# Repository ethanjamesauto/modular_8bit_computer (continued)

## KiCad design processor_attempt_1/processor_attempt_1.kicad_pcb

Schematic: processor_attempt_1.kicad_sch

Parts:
5V_rsns1: 1; R_1206_3216Metric
C1, C2: C; C_1206_3216Metric
C3, C4, C5, C6, C7, C9, C10, C11, C15, C16, C17, C18: 100nF; C_Disc_D3.0mm_W1.6mm_P2.50mm
D1, D17, D25, D33, D41, D49, D50, D51, D52, D53, D54, D55, D56, D57, D58, D59, D60, D61, D62, D63, D64, D65, D66, D67, D68, D69, D70, D71, D72, D73, D74, D75, D76, D77, D78, D79, D80: A0; LED_0603_1608Metric_Pad1.05x0.95mm_HandSolder
D2, D18, D26, D34, D42: A1; LED_0603_1608Metric_Pad1.05x0.95mm_HandSolder
D3, D19, D27, D35, D43: A2; LED_0603_1608Metric_Pad1.05x0.95mm_HandSolder
D4, D20, D28, D36, D44: A3; LED_0603_1608Metric_Pad1.05x0.95mm_HandSolder
D5, D21, D29, D37, D45: A4; LED_0603_1608Metric_Pad1.05x0.95mm_HandSolder
D6, D22, D30, D38, D46: A5; LED_0603_1608Metric_Pad1.05x0.95mm_HandSolder
D7, D23, D31, D39, D47: A6; LED_0603_1608Metric_Pad1.05x0.95mm_HandSolder
D8, D24, D32, D40, D48: A7; LED_0603_1608Metric_Pad1.05x0.95mm_HandSolder
D9: A8; LED_0603_1608Metric_Pad1.05x0.95mm_HandSolder
D10: A9; LED_0603_1608Metric_Pad1.05x0.95mm_HandSolder
D11: A10; LED_0603_1608Metric_Pad1.05x0.95mm_HandSolder
D12: A11; LED_0603_1608Metric_Pad1.05x0.95mm_HandSolder
D13: A12; LED_0603_1608Metric_Pad1.05x0.95mm_HandSolder
D14: A13; LED_0603_1608Metric_Pad1.05x0.95mm_HandSolder
D15: A14; LED_0603_1608Metric_Pad1.05x0.95mm_HandSolder
D16: A15; LED_0603_1608Metric_Pad1.05x0.95mm_HandSolder
D81: 5V_RAW; LED_0603_1608Metric_Pad1.05x0.95mm_HandSolder
J1: Conn_01x03_Pin; PinHeader_1x03_P2.54mm_Vertical
J2: Conn_Coaxial; BNC_TEConnectivity_1478204_Vertical; not fitted
J3: Conn_01x40_Pin; PinHeader_1x40_P2.54mm_Horizontal
J4, J20, J22, J23, J24, J25, J26, J27, J28, J29: Conn_01x08_Pin; PinHeader_1x08_P2.54mm_Vertical
J5, J6: Conn_01x08_Pin; PinHeader_1x08_P2.54mm_Vertical; not fitted
J7, J8, J9, J10, J11, J12, J13, J18, J19: Conn_01x10_Pin; PinHeader_1x10_P2.54mm_Vertical
J14, J15, J16, J17: Conn_01x06_Pin; PinHeader_1x06_P2.54mm_Vertical
J21: DB9_Female_MountingHoles; DSUB-9_Female_Horizontal_P2.77x2.84mm_EdgePinOffset4.94mm_H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
Q1, Q2, Q3, Q4, Q5, Q6, Q7, Q8, Q9, Q10, Q11, Q12: FDG1024NZ; SOT-23-6_Handsoldering
R1, R2: R; R_0603_1608Metric_Pad0.98x0.95mm_HandSolder
R3, R4, R6, R7, R11, R12, R13, R14, R19, R20, R21, R22, R27, R28, R29, R30, R35, R36, R37, R38, R39, R40, R41, R42, R99, R100, R101, R102: 10k; R_0603_1608Metric_Pad0.98x0.95mm_HandSolder
R5, R8, R9, R10, R15, R16, R17, R18, R23, R24, R25, R26, R31, R32, R33, R34, R43, R44, R45, R46, R47, R48, R49, R50: 1k; R_0603_1608Metric_Pad0.98x0.95mm_HandSolder
R103, R104, R105, R106: 0; R_0603_1608Metric_Pad0.98x0.95mm_HandSolder
U1: NE555D; DIP-8_W7.62mm_Socket
U2, U3, U4, U5: 74LS161; DIP-16_W7.62mm_Socket
U6, U7, U25, U26, U27, U44, U45, U47, U54: 74LS574; DIP-20_W7.62mm_Socket
U8, U9, U10, U11: 74LS161; DIP-16_W7.62mm_Socket; not fitted
U12, U13, U14, U15: 74LS257; DIP-16_W7.62mm_Socket; not fitted
U16, U17, U22: 74LS245; DIP-20_W7.62mm_Socket; not fitted
U18, U19: 28C256; DIP-28_W15.24mm_Socket
U20: 74LS574; DIP-20_W7.62mm_Socket; not fitted
U21, U23, U29, U30, U31, U48, U49, U50: 74LS245; DIP-20_W7.62mm_Socket
U24, U40, U41: 74LS273; DIP-20_W7.62mm_Socket
U28: HM62256BLP; DIP-28_W15.24mm
U32, U39: 74LS283; DIP-16_W7.62mm_Socket
U33, U34, U35, U36, U37, U38: DIP-16_W7.62mm_Socket
U42, U56: 74LS04; DIP-14_W7.62mm_Socket
U43: 74HC688; DIP-20_W7.62mm_Socket
U46: HM62256BLP; SOIC-28W_7.5x18.7mm_P1.27mm
U51: 74LS161; SOIC-16_3.9x9.9mm_P1.27mm
U52, U53: 74LS00; DIP-14_W7.62mm_Socket
U55: 74LS30; DIP-14_W7.62mm_Socket
U57, U58, U59, U60: 74LS138; DIP-16_W7.62mm_Socket
U61: 74LVC1G08; SOT-23-6_Handsoldering
r51, r52, r53, r54, r55, r56, r57, r58, r59, r60, r61, r62, r63, r64, r65, r66, r67, r68, r69, r70, r71, r72, r73, r74, r75, r76, r77, r78, r79, r80, r81, r82, r83, r84, r85, r86, r87, r88, r89, r90, r91, r92, r93, r94, r95, r96, r97, r98, r107, r108, r109, r110, r111, r112, r113, r114, r115, r116, r117, r118, r119, r120, r121, r122, r123, r124, r125, r126, r127, r128, r129, r130, r131, r132, r133, r134, r135, r136, r137, r138, r139: 470; R_0603_1608Metric_Pad0.98x0.95mm_HandSolder

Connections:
+3V3: J3.5
+5V: 5V_rsns1.2, C3.1, C4.1, C5.1, C6.1, C7.1, C9.1, C10.1, C11.1, C15.1, C16.1, C17.1, C18.1, R1.1, R5.2, R8.2, R9.2, R10.2, R15.2, R16.2, R17.2, R18.2, R23.2, R24.2, R25.2, R26.2, R31.2, R32.2, R33.2, R34.2, R43.2, R44.2, R45.2, R46.2, R47.2, R48.2, R49.2, R50.2, U1.4 (R), U1.8 (VCC), U2.7 (CEP), U2.16 (VCC), U3.7 (CEP), U3.16 (VCC), U4.7 (CEP), U4.16 (VCC), U5.7 (CEP), U5.16 (VCC), U6.20 (VCC), U7.20 (VCC), U18.28 (VCC), U19.28 (VCC), U21.20 (VCC), U23.20 (VCC), U24.20 (VCC), U25.20 (VCC), U26.20 (VCC), U27.20 (VCC), U28.28 (VCC), U29.20 (VCC), U30.20 (VCC), U31.20 (VCC), U32.16 (VCC), U33.16 (VCC), U34.16 (VCC), U35.16 (VCC), U36.16 (VCC), U37.16 (VCC), U38.16 (VCC), U39.16 (VCC), U40.20 (VCC), U41.20 (VCC), U42.14 (VCC), U43.20 (VCC), U44.20 (VCC), U45.20 (VCC), U46.28 (VCC), U47.20 (VCC), U48.20 (VCC), U49.20 (VCC), U50.20 (VCC), U51.16 (VCC), U52.14 (VCC), U53.14 (VCC), U54.20 (VCC), U55.14 (VCC), U56.14 (VCC), U57.6 (E3), U57.16 (VCC), U58.16 (VCC), U59.16 (VCC), U60.16 (VCC), U61.5 (VCC)
/5V_raw: 5V_rsns1.1, J3.1, U61.4, r139.2
/APB_0: J20.8, U32.4 (S1), U49.18 (B0)
/APB_1: J20.7, U32.1 (S2), U49.17 (B1)
/APB_2: J20.6, U32.13 (S3), U49.16 (B2)
/APB_3: J20.5, U32.10 (S4), U49.15 (B3)
/APB_4: J20.4, U39.4 (S1), U49.14 (B4)
/APB_5: J20.3, U39.1 (S2), U49.13 (B5)
/APB_6: J20.2, U39.13 (S3), U49.12 (B6)
/APB_7: J20.1, U39.10 (S4), U49.11 (B7)
/A_nand_B_0: U50.18 (B0), U52.3
/A_nand_B_1: U50.17 (B1), U52.6
/A_nand_B_2: U50.16 (B2), U52.8
/A_nand_B_3: U50.15 (B3), U52.11
/A_nand_B_4: U50.14 (B4), U53.3
/A_nand_B_5: U50.13 (B5), U53.6
/A_nand_B_6: U50.12 (B6), U53.8
/A_nand_B_7: U50.11 (B7), U53.11
/Aux_Bus_0_LSB: J3.33, J4.1, U21.2 (A0), U25.9 (D7), U26.9 (D7)
/Aux_Bus_1: J3.34, J4.2, U21.3 (A1), U25.8 (D6), U26.8 (D6)
/Aux_Bus_2: J3.35, J4.3, U21.4 (A2), U25.7 (D5), U26.7 (D5)
/Aux_Bus_3: J3.36, J4.4, U21.5 (A3), U25.6 (D4), U26.6 (D4)
/Aux_Bus_4: J3.37, J4.5, U21.6 (A4), U25.5 (D3), U26.5 (D3)
/Aux_Bus_5: J3.38, J4.6, U21.7 (A5), U25.4 (D2), U26.4 (D2)
/Aux_Bus_6: J3.39, J4.7, U21.8 (A6), U25.3 (D1), U26.3 (D1)
/Aux_Bus_7_MSB: J3.40, J4.8, U21.9 (A7), U25.2 (D0), U26.2 (D0)
/CLOCK_to_pc: J1.2, U2.2 (CP), U3.2 (CP), U4.2 (CP), U5.2 (CP), U8.2 (CP), U9.2 (CP), U10.2 (CP), U11.2 (CP)
/Data_Bus_0_LSB: J3.9, J11.2, Q9.3 (D), R43.1, U27.9 (D7)
/Data_Bus_1: J3.10, J11.3, Q9.6 (D), R44.1, U27.8 (D6)
/Data_Bus_2: J3.11, J11.4, Q10.3 (D), R45.1, U27.7 (D5)
/Data_Bus_3: J3.12, J11.5, Q10.6 (D), R46.1, U27.6 (D4)
/Data_Bus_4: J3.13, J11.6, Q11.3 (D), R47.1, U27.5 (D3)
/Data_Bus_5: J3.14, J11.7, Q11.6 (D), R48.1, U27.4 (D2)
/Data_Bus_6: J3.15, J11.8, Q12.3 (D), R49.1, U27.3 (D1)
/Data_Bus_7_MSB: J3.16, J11.9, Q12.6 (D), R50.1, U27.2 (D0)
/INTERNAL_BUS_0: J7.2, J8.2, J12.2, J13.2, J19.8, J21.6, U6.2 (D0), U7.2 (D0), U25.12 (Q7), U26.12 (Q7), U27.12 (Q7), U28.11 (Q0), U29.11 (B7), U30.11 (B7), U31.18 (B0), U38.12 (D3), U40.3 (D0), U41.3 (D0), U44.19 (Q0), U45.19 (Q0), U46.11 (Q0), U47.19 (Q0), U48.18 (B0), U49.2 (A0), U50.2 (A0), U51.3 (D0), U54.19 (Q0), r67.2
/INTERNAL_BUS_1: J7.3, J8.3, J12.3, J13.3, J19.7, J21.7, U6.3 (D1), U7.3 (D1), U25.13 (Q6), U26.13 (Q6), U27.13 (Q6), U28.12 (Q1), U29.12 (B6), U30.12 (B6), U31.17 (B1), U38.10 (D2), U40.4 (D1), U41.4 (D1), U44.18 (Q1), U45.18 (Q1), U46.12 (Q1), U47.18 (Q1), U48.17 (B1), U49.3 (A1), U50.3 (A1), U51.4 (D1), U54.18 (Q1), r68.2
/INTERNAL_BUS_2: J7.4, J8.4, J12.4, J13.4, J19.6, J21.8, U6.4 (D2), U7.4 (D2), U25.14 (Q5), U26.14 (Q5), U27.14 (Q5), U28.13 (Q2), U29.13 (B5), U30.13 (B5), U31.16 (B2), U38.6 (D1), U40.7 (D2), U41.7 (D2), U44.17 (Q2), U45.17 (Q2), U46.13 (Q2), U47.17 (Q2), U48.16 (B2), U49.4 (A2), U50.4 (A2), U51.5 (D2), U54.17 (Q2), r69.2
/INTERNAL_BUS_3: J7.5, J8.5, J12.5, J13.5, J19.5, J21.9, U6.5 (D3), U7.5 (D3), U25.15 (Q4), U26.15 (Q4), U27.15 (Q4), U28.15 (Q3), U29.14 (B4), U30.14 (B4), U31.15 (B3), U38.4 (D0), U40.8 (D3), U41.8 (D3), U44.16 (Q3), U45.16 (Q3), U46.15 (Q3), U47.16 (Q3), U48.15 (B3), U49.5 (A3), U50.5 (A3), U51.6 (D3), U54.16 (Q3), r70.2
/INTERNAL_BUS_4: J7.6, J8.6, J12.6, J13.6, J19.4, J21.5, U6.6 (D4), U7.6 (D4), U25.16 (Q3), U26.16 (Q3), U27.16 (Q3), U28.16 (Q4), U29.15 (B3), U30.15 (B3), U31.14 (B4), U37.12 (D3), U40.13 (D4), U41.13 (D4), U44.15 (Q4), U45.15 (Q4), U46.16 (Q4), U47.15 (Q4), U48.14 (B4), U49.6 (A4), U50.6 (A4), U54.15 (Q4), r71.2
/INTERNAL_BUS_5: J7.7, J8.7, J12.7, J13.7, J19.3, J21.4, U6.7 (D5), U7.7 (D5), U25.17 (Q2), U26.17 (Q2), U27.17 (Q2), U28.17 (Q5), U29.16 (B2), U30.16 (B2), U31.13 (B5), U37.10 (D2), U40.14 (D5), U41.14 (D5), U44.14 (Q5), U45.14 (Q5), U46.17 (Q5), U47.14 (Q5), U48.13 (B5), U49.7 (A5), U50.7 (A5), U54.14 (Q5), r72.2
/INTERNAL_BUS_6: J7.8, J8.8, J12.8, J13.8, J19.2, J21.3, U6.8 (D6), U7.8 (D6), U25.18 (Q1), U26.18 (Q1), U27.18 (Q1), U28.18 (Q6), U29.17 (B1), U30.17 (B1), U31.12 (B6), U37.6 (D1), U40.17 (D6), U41.17 (D6), U44.13 (Q6), U45.13 (Q6), U46.18 (Q6), U47.13 (Q6), U48.12 (B6), U49.8 (A6), U50.8 (A6), U54.13 (Q6), r73.2
/INTERNAL_BUS_7: J7.9, J8.9, J12.9, J13.9, J19.1, J21.2, U6.9 (D7), U7.9 (D7), U25.19 (Q0), U26.19 (Q0), U27.19 (Q0), U28.19 (Q7), U29.18 (B0), U30.18 (B0), U31.11 (B7), U37.4 (D0), U40.18 (D7), U41.18 (D7), U44.12 (Q7), U45.12 (Q7), U46.19 (Q7), U47.12 (Q7), U48.11 (B7), U49.9 (A7), U50.9 (A7), U54.12 (Q7), r74.2
/PC_0: U2.14 (Q0), U16.2 (A0), U30.9 (A7), r51.2
/PC_1: U2.13 (Q1), U16.3 (A1), U18.10 (A0), U19.10 (A0), U30.8 (A6), r52.2
/PC_2: U2.12 (Q2), U16.4 (A2), U18.9 (A1), U19.9 (A1), U30.7 (A5), r53.2
/PC_3: U2.11 (Q3), U16.5 (A3), U18.8 (A2), U19.8 (A2), U30.6 (A4), r54.2
/PC_4: U3.14 (Q0), U16.6 (A4), U18.7 (A3), U19.7 (A3), U30.5 (A3), r55.2
/PC_5: U3.13 (Q1), U16.7 (A5), U18.6 (A4), U19.6 (A4), U30.4 (A2), r56.2
/PC_6: U3.12 (Q2), U16.8 (A6), U18.5 (A5), U19.5 (A5), U30.3 (A1), r57.2
/PC_7: U3.11 (Q3), U16.9 (A7), U18.4 (A6), U19.4 (A6), U30.2 (A0), r58.2
/PC_8: U4.14 (Q0), U18.3 (A7), U19.3 (A7), U29.9 (A7), r59.2
/PC_9: U4.13 (Q1), U18.25 (A8), U19.25 (A8), U29.8 (A6), r60.2
/PC_10: U4.12 (Q2), U18.24 (A9), U19.24 (A9), U29.7 (A5), r61.2
/PC_11: U4.11 (Q3), U18.21 (A10), U19.21 (A10), U29.6 (A4), r62.2
/PC_12: U5.14 (Q0), U18.23 (A11), U19.23 (A11), U29.5 (A3), r63.2
/PC_13: U5.13 (Q1), U18.2 (A12), U19.2 (A12), U29.4 (A2), r64.2
/PC_14: U5.12 (Q2), U18.26 (A13), U19.26 (A13), U29.3 (A1), r65.2
/PC_15: U5.11 (Q3), U18.1 (A14), U19.1 (A14), U29.2 (A0), r66.2
/PC_load_n: U2.9 (~PE), U3.9 (~PE), U4.9 (~PE), U5.9 (~PE)
/RA_0: U32.5 (A1), U40.2 (Q0), U52.2, r83.2
/RA_1: U32.3 (A2), U40.5 (Q1), U52.4, r84.2
/RA_2: U32.14 (A3), U40.6 (Q2), U52.10, r85.2
/RA_3: U32.12 (A4), U40.9 (Q3), U52.12, r86.2
/RA_4: U39.5 (A1), U40.12 (Q4), U53.2, r87.2
/RA_5: U39.3 (A2), U40.15 (Q5), U53.4, r88.2
/RA_6: U39.14 (A3), U40.16 (Q6), U53.10, r89.2
/RA_7: U39.12 (A4), U40.19 (Q7), U53.12, r90.2
/RB_0: U32.6 (B1), U41.2 (Q0), U52.1, r91.2
/RB_1: U32.2 (B2), U41.5 (Q1), U52.5, r92.2
/RB_2: U32.15 (B3), U41.6 (Q2), U52.9, r93.2
/RB_3: U32.11 (B4), U41.9 (Q3), U52.13, r94.2
/RB_4: U39.6 (B1), U41.12 (Q4), U53.1, r95.2
/RB_5: U39.2 (B2), U41.15 (Q5), U53.5, r96.2
/RB_6: U39.15 (B3), U41.16 (Q6), U53.9, r97.2
/RB_7: U39.11 (B4), U41.19 (Q7), U53.13, r98.2
/RC_0: U43.12 (R4), U48.8 (A6), U54.2 (D0), U55.2
/RC_1: U43.14 (R5), U48.6 (A4), U54.3 (D1), U55.1
/RC_2: U43.16 (R6), U48.4 (A2), U54.4 (D2), U55.12
/RC_3: U43.18 (R7), U48.2 (A0), U54.5 (D3), U55.11
/RC_4: U43.3 (R0), U54.6 (D4), U55.6
/RC_5: U43.5 (R1), U54.7 (D5), U55.5
/RC_6: U43.7 (R2), U54.8 (D6), U55.4
/RC_7: U43.9 (R3), U54.9 (D7), U55.3
/RD_0: U43.11 (P4), U47.2 (D0), U48.9 (A7)
/RD_1: U43.13 (P5), U47.3 (D1), U48.7 (A5)
/RD_2: U43.15 (P6), U47.4 (D2), U48.5 (A3)
/RD_3: U43.17 (P7), U47.5 (D3), U48.3 (A1)
/RD_4: U43.2 (P0), U47.6 (D4)
/RD_5: U43.4 (P1), U47.7 (D5)
/RD_6: U43.6 (P2), U47.8 (D6)
/RD_7: U43.8 (P3), U47.9 (D7)
/SMALL_CS2: U46.26 (A13)
/addr_bus_0: J3.17, Q1.3 (D), R5.1
/addr_bus_1: J3.18, Q1.6 (D), R8.1
/addr_bus_2: J3.19, Q2.3 (D), R9.1
/addr_bus_3: J3.20, Q2.6 (D), R10.1
/addr_bus_4: J3.21, Q3.3 (D), R15.1
/addr_bus_5: J3.22, Q3.6 (D), R16.1
/addr_bus_6: J3.23, Q4.3 (D), R17.1
/addr_bus_7: J3.24, Q4.6 (D), R18.1
/addr_bus_8: J3.25, Q5.3 (D), R23.1
/addr_bus_9: J3.26, Q5.6 (D), R24.1
/addr_bus_10: J3.27, Q6.3 (D), R25.1
/addr_bus_11: J3.28, Q6.6 (D), R26.1
/addr_bus_12: J3.29, Q7.3 (D), R31.1
/addr_bus_13: J3.30, Q7.6 (D), R32.1
/addr_bus_14: J3.31, Q8.3 (D), R33.1
/addr_bus_15: J3.32, Q8.6 (D), R34.1
/addr_bus_select_0: R99.2, R103.2, U33.1 (A0), U34.1 (A0), U35.1 (A0), U36.1 (A0), U37.1 (A0), U38.1 (A0)
/addr_bus_select_1: R100.2, R104.2, U33.15 (A1), U34.15 (A1), U35.15 (A1), U36.15 (A1), U37.15 (A1), U38.15 (A1)
/addr_bus_select_2: R101.2, R105.2, U33.14 (A2), U34.14 (A2), U35.14 (A2), U36.14 (A2), U37.14 (A2), U38.14 (A2)
/addr_bus_select_3: R102.2, R106.2, U33.13 (A3), U34.13 (A3), U35.13 (A3), U36.13 (A3), U37.13 (A3), U38.13 (A3)
/addr_oe_n: U33.2 (~CS), U34.2 (~CS), U35.2 (~CS), U36.2 (~CS), U37.2 (~CS), U38.2 (~CS)
/addr_to_driver_0: Q1.5 (G), R4.2, U33.11 (S3_n)
/addr_to_driver_1: Q1.2 (G), R7.2, U33.9 (S2_n)
/addr_to_driver_2: Q2.5 (G), R3.2, U33.7 (S1_n)
/addr_to_driver_3: Q2.2 (G), R6.2, U33.5 (S0_n)
/addr_to_driver_4: Q3.5 (G), R11.2, U35.11 (S3_n)
/addr_to_driver_5: Q3.2 (G), R12.2, U35.9 (S2_n)
/addr_to_driver_6: Q4.5 (G), R13.2, U35.7 (S1_n)
/addr_to_driver_7: Q4.2 (G), R14.2, U35.5 (S0_n)
/addr_to_driver_8: Q5.5 (G), R19.2, U34.11 (S3_n)
/addr_to_driver_9: Q5.2 (G), R20.2, U34.9 (S2_n)
/addr_to_driver_10: Q6.5 (G), R21.2, U34.7 (S1_n)
/addr_to_driver_11: Q6.2 (G), R22.2, U34.5 (S0_n)
/addr_to_driver_12: Q7.5 (G), R27.2, U36.11 (S3_n)
/addr_to_driver_13: Q7.2 (G), R28.2, U36.9 (S2_n)
/addr_to_driver_14: Q8.5 (G), R29.2, U36.7 (S1_n)
/addr_to_driver_15: Q8.2 (G), R30.2, U36.5 (S0_n)
/addr_we_n: U33.3 (~WE), U34.3 (~WE), U35.3 (~WE), U36.3 (~WE)
/clk: J3.3
/ctrl_0: J23.8, J27.8, U57.15 (O0), r138.2
/ctrl_1: J23.7, J27.7, U57.14 (O1), r137.2
/ctrl_2: J23.6, J27.6, U57.13 (O2), r136.2
/ctrl_3: J23.5, J27.5, U57.12 (O3), r135.2
/ctrl_4: J23.4, J27.4, U57.11 (O4), r134.2
/ctrl_5: J23.3, J27.3, U57.10 (O5), r133.2
/ctrl_6: J23.2, J27.2, U57.9 (O6), r132.2
/ctrl_7: J23.1, J27.1, U57.7 (O7), r131.2
/ctrl_8: J22.8, J24.8, U58.15 (O0), r130.2
/ctrl_9: J22.7, J24.7, U58.14 (O1), r129.2
/ctrl_10: J22.6, J24.6, U58.13 (O2), r128.2
/ctrl_11: J22.5, J24.5, U58.12 (O3), r127.2
/ctrl_12: J22.4, J24.4, U58.11 (O4), r126.2
/ctrl_13: J22.3, J24.3, U58.10 (O5), r125.2
/ctrl_14: J22.2, J24.2, U58.9 (O6), r124.2
/ctrl_15: J22.1, J24.1, U58.7 (O7), r123.2
/ctrl_16: J26.8, J28.8, U59.15 (O0), r107.2
/ctrl_17: J26.7, J28.7, U59.14 (O1), r108.2
/ctrl_18: J26.6, J28.6, U59.13 (O2), r109.2
/ctrl_19: J26.5, J28.5, U59.12 (O3), r110.2
/ctrl_20: J26.4, J28.4, U59.11 (O4), r111.2
/ctrl_21: J26.3, J28.3, U59.10 (O5), r112.2
/ctrl_22: J26.2, J28.2, U59.9 (O6), r113.2
/ctrl_23: J26.1, J28.1, U59.7 (O7), r114.2
/ctrl_24: J25.8, J29.8, U60.15 (O0), r115.2
/ctrl_25: J25.7, J29.7, U60.14 (O1), r116.2
/ctrl_26: J25.6, J29.6, U60.13 (O2), r117.2
/ctrl_27: J25.5, J29.5, U60.12 (O3), r118.2
/ctrl_28: J25.4, J29.4, U60.11 (O4), r119.2
/ctrl_29: J25.3, J29.3, U60.10 (O5), r120.2
/ctrl_30: J25.2, J29.2, U60.9 (O6), r121.2
/ctrl_31: J25.1, J29.1, U60.7 (O7), r122.2
/current_sense_output: U61.1
/data_to_driver_0: Q9.5 (G), R35.2, U38.11 (S3_n)
/data_to_driver_1: Q9.2 (G), R36.2, U38.9 (S2_n)
/data_to_driver_2: Q10.5 (G), R37.2, U38.7 (S1_n)
/data_to_driver_3: Q10.2 (G), R38.2, U38.5 (S0_n)
/data_to_driver_4: Q11.5 (G), R39.2, U37.11 (S3_n)
/data_to_driver_5: Q11.2 (G), R40.2, U37.9 (S2_n)
/data_to_driver_6: Q12.5 (G), R41.2, U37.7 (S1_n)
/data_to_driver_7: Q12.2 (G), R42.2, U37.5 (S0_n)
/data_we_n: U37.3 (~WE), U38.3 (~WE)
/decoder_neg_clock: U60.5 (E2)
/decoder_pos_clock: U59.6 (E3)
/instruction_0: J18.2, U18.11 (D0), U19.11 (D0), U20.19 (Q0), U21.18 (B0), U22.18 (B0), U23.2 (A0), U24.3 (D0), U31.2 (A0), r75.2
/instruction_1: J18.3, U18.12 (D1), U19.12 (D1), U20.18 (Q1), U21.17 (B1), U22.17 (B1), U23.3 (A1), U24.4 (D1), U31.3 (A1), r76.2
/instruction_2: J18.4, U18.13 (D2), U19.13 (D2), U20.17 (Q2), U21.16 (B2), U22.16 (B2), U23.4 (A2), U24.7 (D2), U31.4 (A2), r77.2
/instruction_3: J18.5, U18.15 (D3), U19.15 (D3), U20.16 (Q3), U21.15 (B3), U22.15 (B3), U23.5 (A3), U24.8 (D3), U31.5 (A3), r78.2
/instruction_4: J18.6, U18.16 (D4), U19.16 (D4), U20.15 (Q4), U21.14 (B4), U22.14 (B4), U23.6 (A4), U24.13 (D4), U31.6 (A4), r79.2
/instruction_5: J18.7, U18.17 (D5), U19.17 (D5), U20.14 (Q5), U21.13 (B5), U22.13 (B5), U23.7 (A5), U24.14 (D5), U31.7 (A5), r80.2
/instruction_6: J18.8, U18.18 (D6), U19.18 (D6), U20.13 (Q6), U21.12 (B6), U22.12 (B6), U23.8 (A6), U24.17 (D6), U31.8 (A6), r81.2
/instruction_7: J18.9, U18.19 (D7), U19.19 (D7), U20.12 (Q7), U21.11 (B7), U22.11 (B7), U23.9 (A7), U24.18 (D7), U31.9 (A7), r82.2
/instruction_valid_n: U57.4 (E1), U58.4 (E1), U59.4 (E1), U60.4 (E1)
/mar_0: U28.10 (A0), U45.2 (D0), U46.10 (A0)
/mar_1: U28.9 (A1), U45.3 (D1), U46.9 (A1)
/mar_2: U28.8 (A2), U45.4 (D2), U46.8 (A2)
/mar_3: U28.7 (A3), U45.5 (D3), U46.7 (A3)
/mar_4: U28.6 (A4), U45.6 (D4), U46.6 (A4)
/mar_5: U28.5 (A5), U45.7 (D5), U46.5 (A5)
/mar_6: U28.4 (A6), U45.8 (D6), U46.4 (A6)
/mar_7: U28.3 (A7), U45.9 (D7), U46.3 (A7)
/mar_8: U28.25 (A8), U44.2 (D0), U46.25 (A8)
/mar_9: U28.24 (A9), U44.3 (D1), U46.24 (A9)
/mar_10: U28.21 (A10), U44.4 (D2), U46.21 (A10)
/mar_11: U28.23 (A11), U44.5 (D3), U46.23 (A11)
/mar_12: U28.2 (A12), U44.6 (D4), U46.2 (A12)
/mar_13: U28.26 (A13), U44.7 (D5)
/mar_14: U28.1 (A14), U44.8 (D6)
/mar_15: U44.9 (D7)
/pc_reset_n: U2.1 (~MR), U3.1 (~MR), U4.1 (~MR), U5.1 (~MR)
/reset_n: J3.4
/to_PC_0: J9.2, U2.3 (D0), U6.19 (Q0), U8.3 (D0), U33.12 (D3)
/to_PC_1: J9.3, U2.4 (D1), U6.18 (Q1), U8.4 (D1), U33.10 (D2)
/to_PC_2: J9.4, U2.5 (D2), U6.17 (Q2), U8.5 (D2), U33.6 (D1)
/to_PC_3: J9.5, U2.6 (D3), U6.16 (Q3), U8.6 (D3), U33.4 (D0)
/to_PC_4: J9.6, U3.3 (D0), U6.15 (Q4), U9.3 (D0), U35.12 (D3)
/to_PC_5: J9.7, U3.4 (D1), U6.14 (Q5), U9.4 (D1), U35.10 (D2)
/to_PC_6: J9.8, U3.5 (D2), U6.13 (Q6), U9.5 (D2), U35.6 (D1)
/to_PC_7: J9.9, U3.6 (D3), U6.12 (Q7), U9.6 (D3), U35.4 (D0)
/to_PC_8: J10.2, U4.3 (D0), U7.19 (Q0), U10.3 (D0), U34.12 (D3)
/to_PC_9: J10.3, U4.4 (D1), U7.18 (Q1), U10.4 (D1), U34.10 (D2)
/to_PC_10: J10.4, U4.5 (D2), U7.17 (Q2), U10.5 (D2), U34.6 (D1)
/to_PC_11: J10.5, U4.6 (D3), U7.16 (Q3), U10.6 (D3), U34.4 (D0)
/to_PC_12: J10.6, U5.3 (D0), U7.15 (Q4), U11.3 (D0), U36.12 (D3)
/to_PC_13: J10.7, U5.4 (D1), U7.14 (Q5), U11.4 (D1), U36.10 (D2)
/to_PC_14: J10.8, U5.5 (D2), U7.13 (Q6), U11.5 (D2), U36.6 (D1)
/to_PC_15: J10.9, U5.6 (D3), U7.12 (Q7), U11.6 (D3), U36.4 (D0)
/to_insdec_0: U23.18 (B0)
/to_insdec_1: U23.17 (B1)
/to_insdec_2: U23.16 (B2)
/to_insdec_3: U23.15 (B3)
/to_insdec_4: U23.14 (B4), U57.1 (A0), U58.1 (A0)
/to_insdec_5: U23.13 (B5), U57.2 (A1), U58.2 (A1)
/to_insdec_6: U23.12 (B6), U57.3 (A2), U58.3 (A2)
/to_insdec_7: U23.11 (B7), U57.5 (E2), U58.6 (E3)
/to_insdec_8: U24.2 (Q0), U59.1 (A0), U60.1 (A0)
/to_insdec_9: U24.5 (Q1), U59.2 (A1), U60.2 (A1)
/to_insdec_10: U24.6 (Q2), U59.3 (A2), U60.3 (A2)
/to_insdec_11: U24.9 (Q3), U59.5 (E2), U60.6 (E3)
/to_insdec_12: U24.12 (Q4)
/to_insdec_13: U24.15 (Q5)
/to_insdec_14: U24.16 (Q6)
/to_insdec_15: U24.19 (Q7)
GND: C1.2, C2.2, C3.2, C4.2, C5.2, C6.2, C7.2, C9.2, C10.2, C11.2, C15.2, C16.2, C17.2, C18.2, D1.1 (K), D2.1 (K), D3.1 (K), D4.1 (K), D5.1 (K), D6.1 (K), D7.1 (K), D8.1 (K), D9.1 (K), D10.1 (K), D11.1 (K), D12.1 (K), D13.1 (K), D14.1 (K), D15.1 (K), D16.1 (K), D17.1 (K), D18.1 (K), D19.1 (K), D20.1 (K), D21.1 (K), D22.1 (K), D23.1 (K), D24.1 (K), D25.1 (K), D26.1 (K), D27.1 (K), D28.1 (K), D29.1 (K), D30.1 (K), D31.1 (K), D32.1 (K), D33.1 (K), D34.1 (K), D35.1 (K), D36.1 (K), D37.1 (K), D38.1 (K), D39.1 (K), D40.1 (K), D41.1 (K), D42.1 (K), D43.1 (K), D44.1 (K), D45.1 (K), D46.1 (K), D47.1 (K), D48.1 (K), D49.1 (K), D50.1 (K), D51.1 (K), D52.1 (K), D53.1 (K), D54.1 (K), D55.1 (K), D56.1 (K), D57.1 (K), D58.1 (K), D59.1 (K), D60.1 (K), D61.1 (K), D62.1 (K), D63.1 (K), D64.1 (K), D65.1 (K), D66.1 (K), D67.1 (K), D68.1 (K), D69.1 (K), D70.1 (K), D71.1 (K), D72.1 (K), D73.1 (K), D74.1 (K), D75.1 (K), D76.1 (K), D77.1 (K), D78.1 (K), D79.1 (K), D80.1 (K), D81.1 (K), J3.2, J21.0 (PAD), Q1.1 (S), Q1.4 (S), Q2.1 (S), Q2.4 (S), Q3.1 (S), Q3.4 (S), Q4.1 (S), Q4.4 (S), Q5.1 (S), Q5.4 (S), Q6.1 (S), Q6.4 (S), Q7.1 (S), Q7.4 (S), Q8.1 (S), Q8.4 (S), Q9.1 (S), Q9.4 (S), Q10.1 (S), Q10.4 (S), Q11.1 (S), Q11.4 (S), Q12.1 (S), Q12.4 (S), R3.1, R4.1, R6.1, R7.1, R11.1, R12.1, R13.1, R14.1, R19.1, R20.1, R21.1, R22.1, R27.1, R28.1, R29.1, R30.1, R35.1, R36.1, R37.1, R38.1, R39.1, R40.1, R41.1, R42.1, R99.1, R100.1, R101.1, R102.1, U1.1 (GND), U2.8 (GND), U3.8 (GND), U4.8 (GND), U5.8 (GND), U6.10 (GND), U7.10 (GND), U18.14 (GND), U19.14 (GND), U21.10 (GND), U23.10 (GND), U24.10 (GND), U25.10 (GND), U26.10 (GND), U27.10 (GND), U28.14 (GND), U29.10 (GND), U30.10 (GND), U31.10 (GND), U32.8 (GND), U33.8 (GND), U34.8 (GND), U35.8 (GND), U36.8 (GND), U37.8 (GND), U38.8 (GND), U39.8 (GND), U40.10 (GND), U41.10 (GND), U42.7 (GND), U43.10 (GND), U44.10 (GND), U45.10 (GND), U46.14 (GND), U47.10 (GND), U48.10 (GND), U49.10 (GND), U50.10 (GND), U51.8 (GND), U52.7 (GND), U53.7 (GND), U54.10 (GND), U55.7 (GND), U56.7 (GND), U57.8 (GND), U58.5 (E2), U58.8 (GND), U59.8 (GND), U60.8 (GND), U61.2
unnamed: D1.2 (A), r51.1
unnamed: D2.2 (A), r52.1
unnamed: D3.2 (A), r53.1
unnamed: D4.2 (A), r54.1
unnamed: D5.2 (A), r55.1
unnamed: D6.2 (A), r56.1
unnamed: D7.2 (A), r57.1
unnamed: D8.2 (A), r58.1
unnamed: D9.2 (A), r59.1
unnamed: D10.2 (A), r60.1
unnamed: D11.2 (A), r61.1
unnamed: D12.2 (A), r62.1
unnamed: D13.2 (A), r63.1
unnamed: D14.2 (A), r64.1
unnamed: D15.2 (A), r65.1
unnamed: D16.2 (A), r66.1
unnamed: D17.2 (A), r67.1
unnamed: D18.2 (A), r68.1
unnamed: D19.2 (A), r69.1
unnamed: D20.2 (A), r70.1
unnamed: D21.2 (A), r71.1
unnamed: D22.2 (A), r72.1
unnamed: D23.2 (A), r73.1
unnamed: D24.2 (A), r74.1
unnamed: D25.2 (A), r75.1
unnamed: D26.2 (A), r76.1
unnamed: D27.2 (A), r77.1
unnamed: D28.2 (A), r78.1
unnamed: D29.2 (A), r79.1
unnamed: D30.2 (A), r80.1
unnamed: D31.2 (A), r81.1
unnamed: D32.2 (A), r82.1
unnamed: D33.2 (A), r83.1
unnamed: D34.2 (A), r84.1
unnamed: D35.2 (A), r85.1
unnamed: D36.2 (A), r86.1
unnamed: D37.2 (A), r87.1
unnamed: D38.2 (A), r88.1
unnamed: D39.2 (A), r89.1
unnamed: D40.2 (A), r90.1
unnamed: D41.2 (A), r91.1
unnamed: D42.2 (A), r92.1
unnamed: D43.2 (A), r93.1
unnamed: D44.2 (A), r94.1
unnamed: D45.2 (A), r95.1
unnamed: D46.2 (A), r96.1
unnamed: D47.2 (A), r97.1
unnamed: D48.2 (A), r98.1
unnamed: D49.2 (A), r107.1
unnamed: D50.2 (A), r108.1
unnamed: D51.2 (A), r109.1
unnamed: D52.2 (A), r110.1
unnamed: D53.2 (A), r111.1
unnamed: D54.2 (A), r112.1
unnamed: D55.2 (A), r113.1
unnamed: D56.2 (A), r114.1
unnamed: D57.2 (A), r115.1
unnamed: D58.2 (A), r116.1
unnamed: D59.2 (A), r117.1
unnamed: D60.2 (A), r118.1
unnamed: D61.2 (A), r119.1
unnamed: D62.2 (A), r120.1
unnamed: D63.2 (A), r121.1
unnamed: D64.2 (A), r122.1
unnamed: D65.2 (A), r123.1
unnamed: D66.2 (A), r124.1
unnamed: D67.2 (A), r125.1
unnamed: D68.2 (A), r126.1
unnamed: D69.2 (A), r127.1
unnamed: D70.2 (A), r128.1
unnamed: D71.2 (A), r129.1
unnamed: D72.2 (A), r130.1
unnamed: D73.2 (A), r131.1
unnamed: D74.2 (A), r132.1
unnamed: D75.2 (A), r133.1
unnamed: D76.2 (A), r134.1
unnamed: D77.2 (A), r135.1
unnamed: D78.2 (A), r136.1
unnamed: D79.2 (A), r137.1
unnamed: D80.2 (A), r138.1
unnamed: D81.2 (A), r139.1
unnamed: J1.1, J2.1 (In)
unnamed: J1.3, U1.3 (Q)
unnamed: C1.1, U1.5 (CV)
unnamed: R1.2, R2.1, U1.7 (DIS)
unnamed: C2.1, R2.2, U1.2 (TR), U1.6 (THR)
unnamed: U2.15 (TC), U3.10 (CET)
unnamed: U3.15 (TC), U4.10 (CET)
unnamed: U4.15 (TC), U5.10 (CET)
unnamed: U8.15 (TC), U9.10 (CET)
unnamed: U8.1 (~MR), U9.1 (~MR), U10.1 (~MR), U11.1 (~MR)
unnamed: U8.9 (~PE), U9.9 (~PE), U10.9 (~PE), U11.9 (~PE)
unnamed: U9.15 (TC), U10.10 (CET)
unnamed: U10.15 (TC), U11.10 (CET)
unnamed: U16.11 (B7), U17.11 (B7)
unnamed: U16.12 (B6), U17.12 (B6)
unnamed: U16.13 (B5), U17.13 (B5)
unnamed: U16.14 (B4), U17.14 (B4)
unnamed: U16.15 (B3), U17.15 (B3)
unnamed: U16.16 (B2), U17.16 (B2)
unnamed: U16.17 (B1), U17.17 (B1)
unnamed: U16.18 (B0), U17.18 (B0)
unnamed: U8.14 (Q0), U17.2 (A0)
unnamed: U8.13 (Q1), U17.3 (A1)
unnamed: U8.12 (Q2), U17.4 (A2)
unnamed: U8.11 (Q3), U17.5 (A3)
unnamed: U9.14 (Q0), U17.6 (A4)
unnamed: U9.13 (Q1), U17.7 (A5)
unnamed: U9.12 (Q2), U17.8 (A6)
unnamed: U9.11 (Q3), U17.9 (A7)
unnamed: U32.9 (C4), U39.7 (C0)
unnamed: R103.1, U51.14 (Q0)
unnamed: R104.1, U51.13 (Q1)
unnamed: R105.1, U51.12 (Q2)
unnamed: R106.1, U51.11 (Q3)

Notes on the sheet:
Will exist on breakout PCB to be installed above other PC
To be installed on breakout PCB (same PCB as the other PC)
CARD EDGE INTERFACE
Will exist on breakout PCB to be soldered directly above other ROM
BOLTONE OSCILLATOR
positive clocked destinations
ADDRESS BUS DRIVERS
ACTUAL CHIP IS INA281B2
DATA Bus clocked instruction
AUX Bus direct instruction
16b PC
Instruction Expander
instruction
DATA Bus direct instruction
A PLUS B OPERATION
INTERNAL DATA BUS LEDS
Instruction Decoders
A and B REGISTERS
source selector upper
inverted clocked destinations
Instruction Memory
16b aux PC
16b builder
source selector lower
AUX DIRECT EXECUTE
EXTERNAL OSCILLATOR
32k Cache
LED indicators
PROGRAM COUNTER STATE LEDS
OUTPUT PAGE SELECT
Program Counter Select
Equals and comparison logic
WARNING: CHIP USED FOR FOOTPRINT ONLY
General Purpose Inverters
NAND OPERATION
to_insdec
DATA BUS DRIVERS
TODO: differential pair???

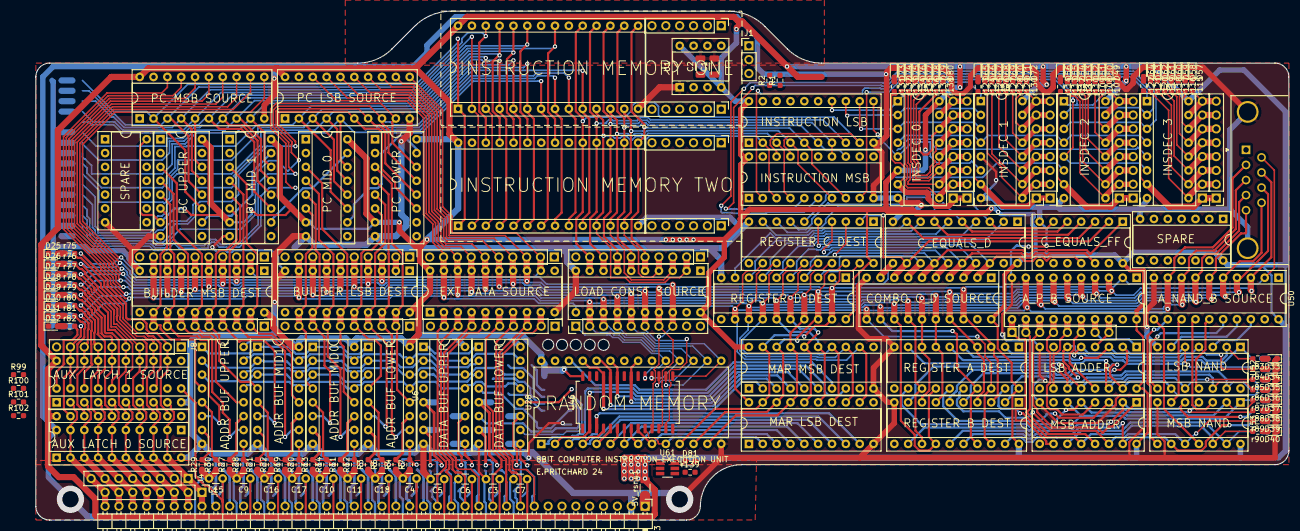
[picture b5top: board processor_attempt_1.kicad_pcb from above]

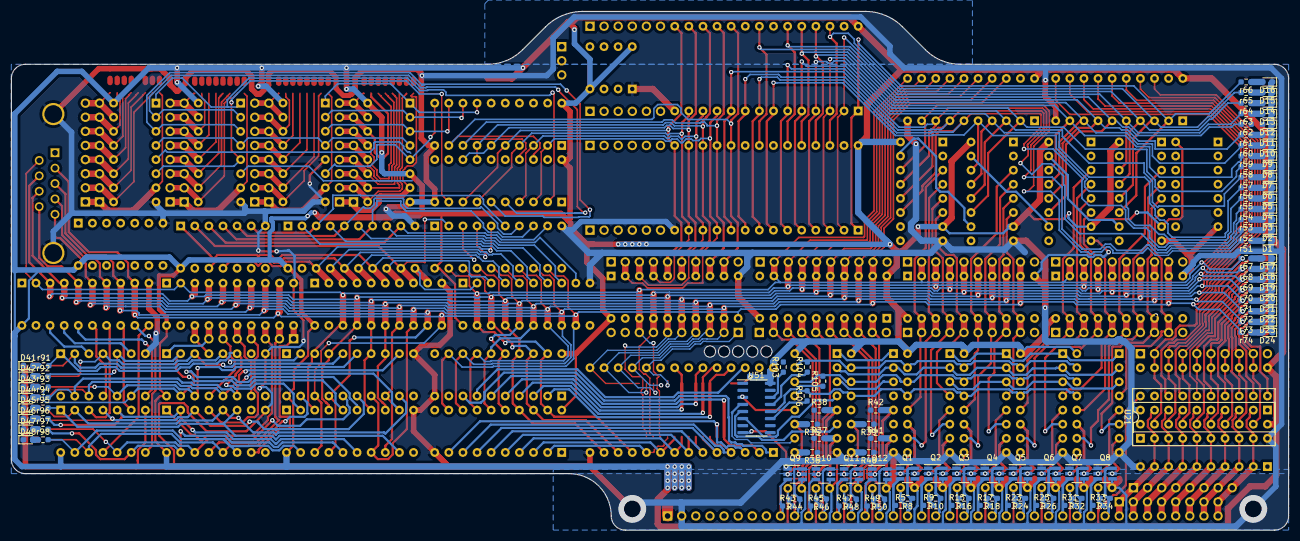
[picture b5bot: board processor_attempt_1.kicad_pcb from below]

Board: 2 copper layers, 229.9 x 93.3 mm, 323 parts (114 on the bottom side), 314 nets.

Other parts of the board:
J4#2: Conn_01x08_Pin; PinHeader_1x08_P2.54mm_Vertical
